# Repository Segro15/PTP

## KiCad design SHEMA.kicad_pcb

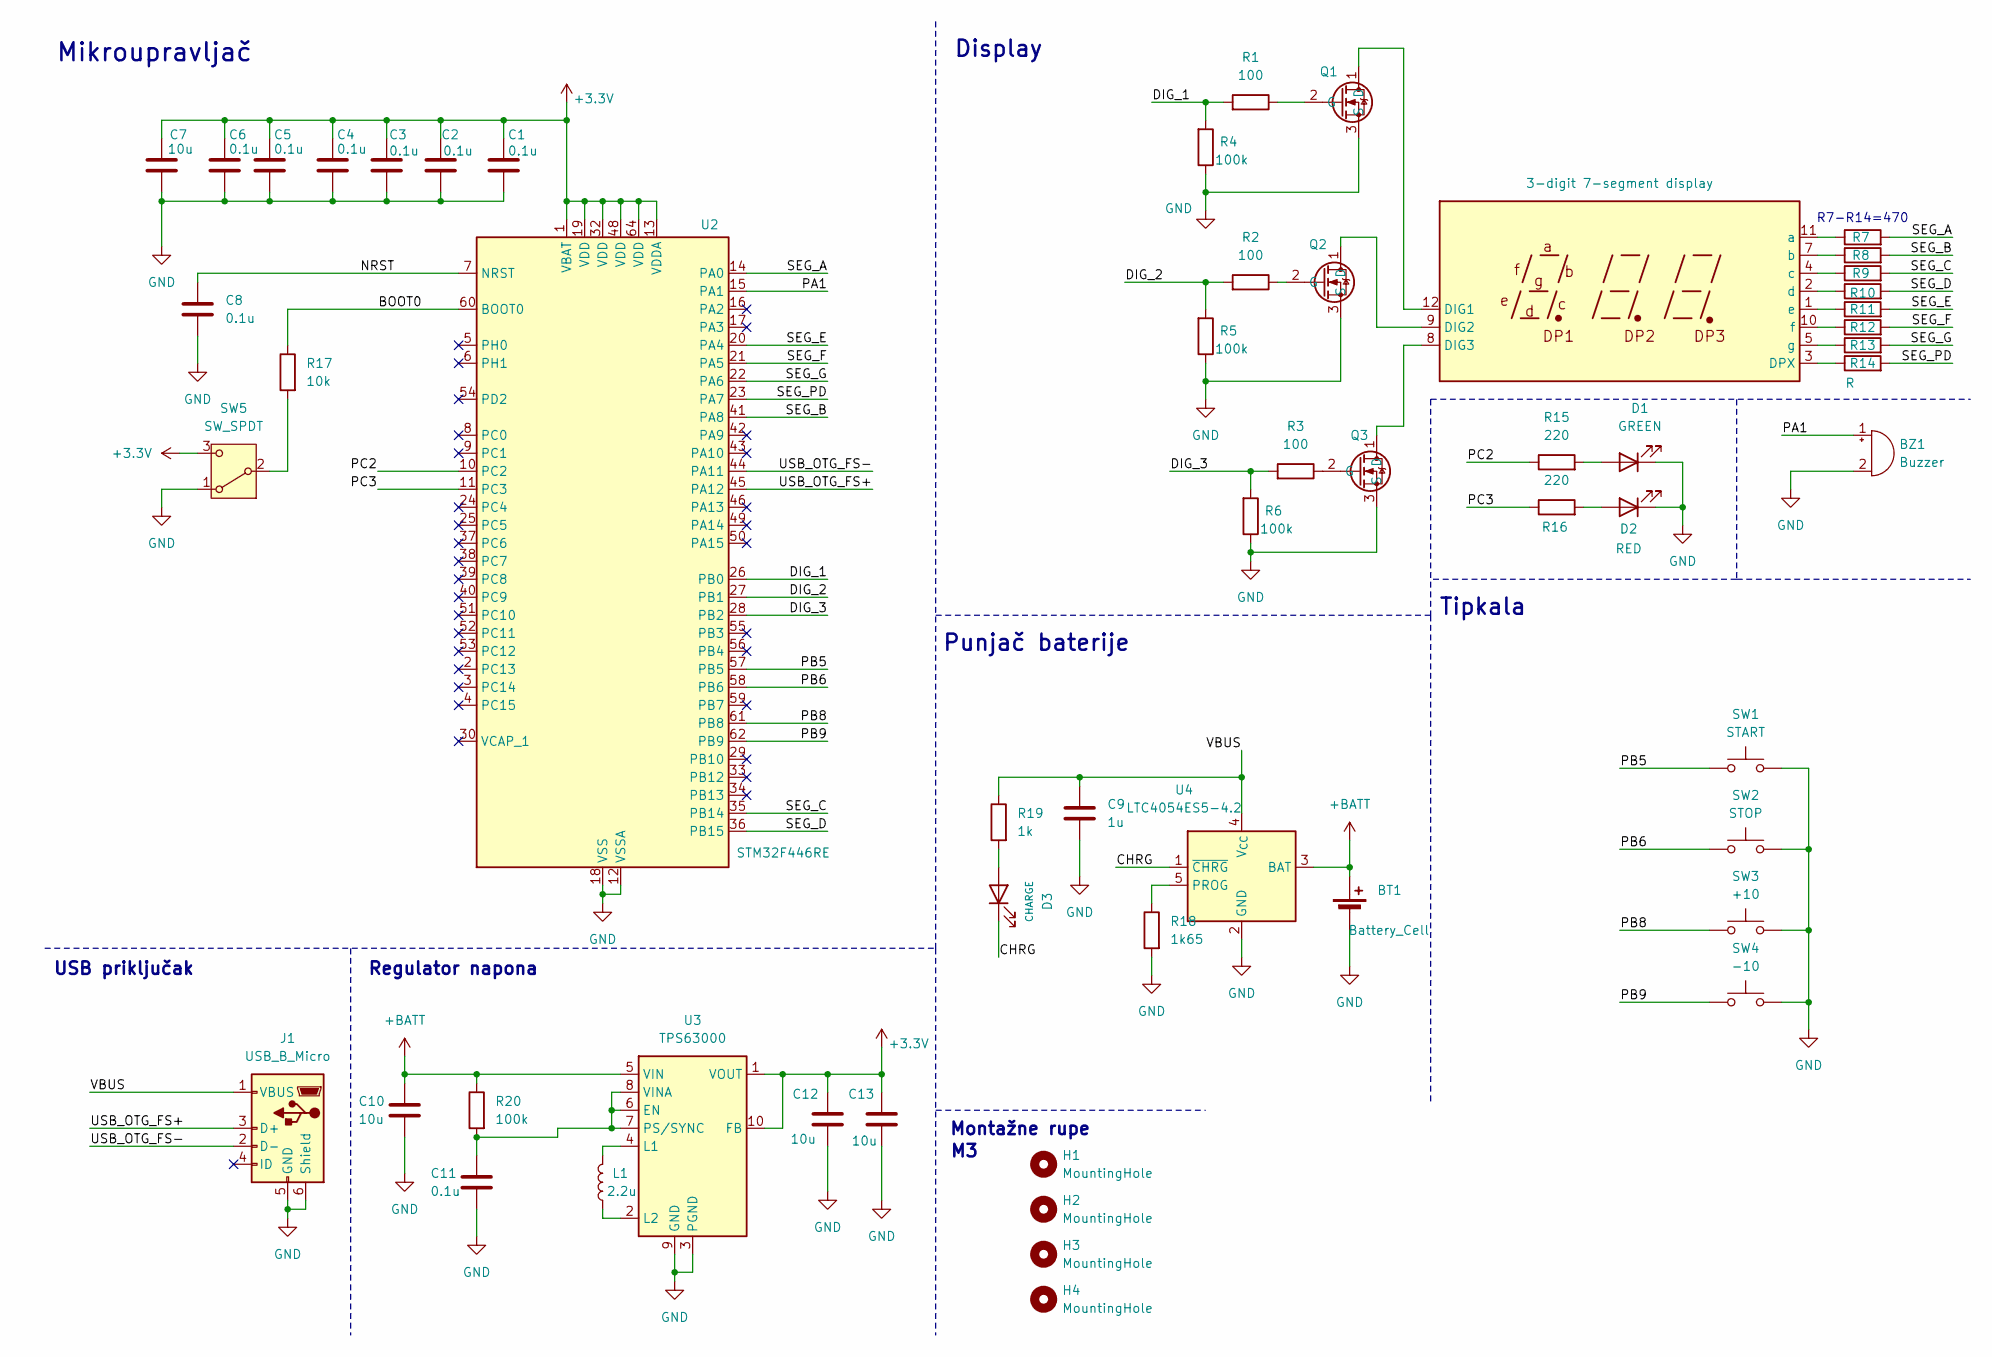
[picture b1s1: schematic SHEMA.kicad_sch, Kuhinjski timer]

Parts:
BT1: Battery_Cell; BatteryHolder_Keystone_1042_1x18650
BZ1: Buzzer; MagneticBuzzer_PUI_AT-0927-TT-6-R
C1, C2, C3, C4, C5, C6, C8, C11: 0.1u; C_0402_1005Metric
C7, C10, C12, C13: 10u; C_0603_1608Metric
C9: 1u; C_0402_1005Metric
D1: GREEN; LED_D5.0mm_FlatTop
D2: RED; LED_D5.0mm_FlatTop
D3: CHARGE; LED_D5.0mm_FlatTop
H1, H2, H3, H4: MountingHole; MountingHole_3.2mm_M3_DIN965
J1: USB_B_Micro; USB_Micro-B_Wuerth_629105150521
L1: 2.2u; L_TDK_MLZ2012_h0.85mm
Q1, Q2, Q3: BS170; TO-92
R1, R2, R3: 100; R_1206_3216Metric
R4, R5, R6: 100k; R_1206_3216Metric
R7, R8, R9, R10, R11, R12, R13, R14: R; R_1206_3216Metric
R15, R16: 220; R_0805_2012Metric
R17: 10k; R_0805_2012Metric
R18: 1k65; R_0805_2012Metric
R19: 1k; R_0805_2012Metric
R20: 100k; R_0805_2012Metric
SW1: START; SW_PUSH_1P1T_6x3.5mm_H4.3_APEM_MJTP1243
SW2: STOP; SW_PUSH_1P1T_6x3.5mm_H4.3_APEM_MJTP1243
SW3: +10; SW_PUSH_1P1T_6x3.5mm_H4.3_APEM_MJTP1243
SW4: -10; SW_PUSH_1P1T_6x3.5mm_H4.3_APEM_MJTP1243
SW5: SW_SPDT; SW_SPDT_PCM12
U1: 3-digit 7-segment display; LED_BA56-12SRWA
U2: STM32F446RE; LQFP-64_10x10mm_P0.5mm
U3: TPS63000; Texas_DRC0010J_ThermalVias
U4: LTC4054ES5-4.2; TSOT-23-5

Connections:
+3.3V: C1.1, C2.1, C3.1, C4.1, C5.1, C6.1, C7.1, C12.1, C13.1, SW5.3 (C), U2.1 (VBAT), U2.13 (VDDA), U2.19 (VDD), U2.32 (VDD), U2.48 (VDD), U2.64 (VDD), U3.1 (VOUT), U3.10 (FB); also elsewhere on the board
+BATT: BT1.1 (+), C10.1, R20.1, U3.5 (VIN), U4.3 (BAT); also elsewhere on the board
/BOOT0: R17.1, U2.60 (BOOT0)
/CHRG: D3.1 (K), U4.1 (~CHRG)
/DIG_1: R1.2, R4.2, U2.26 (PB0)
/DIG_2: R2.2, R5.2, U2.27 (PB1)
/DIG_3: R3.2, R6.2, U2.28 (PB2)
/NRST: C8.1, U2.7 (NRST)
/PA1: BZ1.1 (+), U2.15 (PA1)
/PB5: SW1.1, U2.57 (PB5)
/PB6: SW2.1, U2.58 (PB6)
/PB8: SW3.1, U2.61 (PB8)
/PB9: SW4.1, U2.62 (PB9)
/PC2: R15.1, U2.10 (PC2)
/PC3: R16.1, U2.11 (PC3)
/SEG_A: R7.2, U2.14 (PA0)
/SEG_B: R8.2, U2.41 (PA8)
/SEG_C: R9.2, U2.35 (PB14)
/SEG_D: R10.2, U2.36 (PB15)
/SEG_E: R11.2, U2.20 (PA4)
/SEG_F: R12.2, U2.21 (PA5)
/SEG_G: R13.2, U2.22 (PA6)
/SEG_PD: R14.2, U2.23 (PA7)
/USB_OTG_FS+: J1.3 (D+), U2.45 (PA12)
/USB_OTG_FS-: J1.2 (D-), U2.44 (PA11)
/VBUS: C9.1, J1.1 (VBUS), R19.1, U4.4 (V_{CC})
GND: BT1.2 (-), BZ1.2 (-), C1.2, C2.2, C3.2, C4.2, C5.2, C6.2, C7.2, C8.2, C9.2, C10.2, C11.2, C12.2, C13.2, D1.1 (K), D2.1 (K), J1.5 (GND), J1.6 (Shield), Q1.3 (S), Q2.3 (S), Q3.3 (S), R4.1, R5.1, R6.1, R18.2, SW1.2, SW2.2, SW3.2, SW4.2, SW5.1 (A), U2.12 (VSSA), U2.18 (VSS), U2.31 (VSS), U2.47 (VSS), U2.63 (VSS), U3.3 (PGND), U3.9 (GND), U3.11 (PGND), U4.2 (GND); also elsewhere on the board
unnamed: D1.2 (A), R15.2
unnamed: D2.2 (A), R16.2
unnamed: D3.2 (A), R19.2
unnamed: Q1.1 (D), U1.12 (DIG1)
unnamed: Q1.2 (G), R1.1
unnamed: Q2.1 (D), U1.9 (DIG2)
unnamed: Q2.2 (G), R2.1
unnamed: Q3.1 (D), U1.8 (DIG3)
unnamed: Q3.2 (G), R3.1
unnamed 36: R17.2, SW5.2 (B); also elsewhere on the board
unnamed: R14.1, U1.3 (DPX)
unnamed: R7.1, U1.11 (a)
unnamed: R8.1, U1.7 (b)
unnamed: R9.1, U1.4 (c)
unnamed: R10.1, U1.2 (d)
unnamed: R11.1, U1.1 (e)
unnamed: R12.1, U1.10 (f)
unnamed: R13.1, U1.5 (g)
unnamed: C11.1, R20.2, U3.6 (EN), U3.7 (PS/SYNC), U3.8 (VINA)
unnamed: L1.2, U3.4 (L1)
unnamed: L1.1, U3.2 (L2)
unnamed: R18.1, U4.5 (PROG)

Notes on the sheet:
R7-R14=470
Mikroupravljač
Tipkala
Display
Regulator napona
USB priključak
Punjač baterije
Montažne rupe

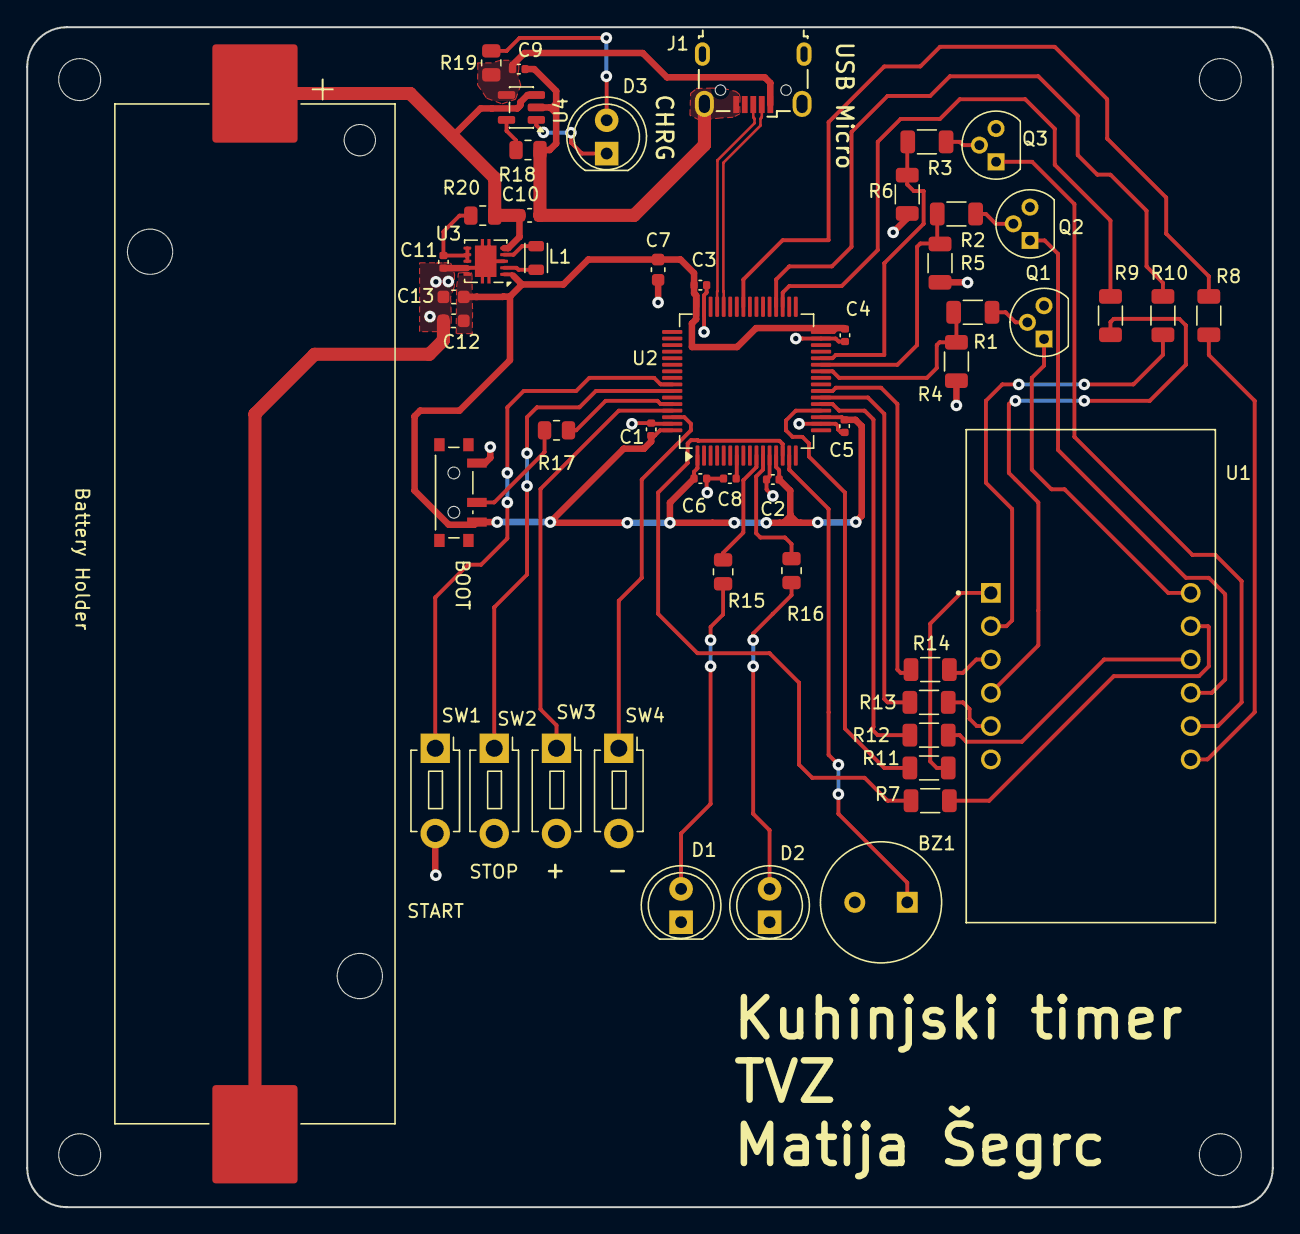
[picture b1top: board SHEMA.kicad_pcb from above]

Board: 2 copper layers, 95.0 x 90.0 mm, 56 parts (0 on the bottom side), 49 nets.

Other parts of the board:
BOOT: SW_SPDT; SW_SPDT_PCM12
Battery Holder: Battery_Cell; BatteryHolder_Keystone_1042_1x18650

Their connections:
+3.3V: BOOT.3 (C); also elsewhere on the board
+BATT: Battery Holder.1 (+); also elsewhere on the board
GND: BOOT.1 (A), Battery Holder.2 (-); also elsewhere on the board
unnamed 36: BOOT.2 (B); also elsewhere on the board

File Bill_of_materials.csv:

Reference;Quantity;Manufacturers Part Number;Manufacturer;Value;Footprint
BT1;1;1042;Keystone;~;Battery:BatteryHolder_Keystone_1042_1x18650
BZ1;1;AT?0927?TT?6?R;PUIaudio;~;Buzzer_Beeper:MagneticBuzzer_PUI_AT-0927-TT-6-R
C1,C2,C3,C4,C5,C6,C8,C11;8;~;~;0.1u;Capacitor_SMD:C_0402_1005Metric
C7,C10,C12,C13;4;~;~;10u;Capacitor_SMD:C_0603_1608Metric
C9;1;~;~;1u;Capacitor_SMD:C_0402_1005Metric
D1,D2,D3;3;~;~;~;LED_THT:LED_D5.0mm_FlatTop
J1;1;6,29105E+11;Wuerth;USB_B_Micro;Connector_USB:USB_Micro-B_Wuerth_629105150521
L1;1;MLZ2012;TDK;2.2u;Inductor_SMD:L_TDK_MLZ2012_h0.85mm
Q1,Q2,Q3;3;BS170-D26Z;Onsemi;BS170;Package_TO_SOT_THT:TO-92
R1,R2,R3;3;~;~;100;Resistor_SMD:R_1206_3216Metric
R4,R5,R6,R20;4;~;~;100k;Resistor_SMD:R_1206_3216Metric
R7,R8,R9,R10,R11,R12,R13,R14;8;~;~;470;Resistor_SMD:R_1206_3216Metric
R15,R16;2;~;~;220;Resistor_SMD:R_0805_2012Metric
R17;1;~;~;10k;Resistor_SMD:R_0805_2012Metric
R18;1;~;~;1k65;Resistor_SMD:R_0805_2012Metric
R19;1;~;~;1k;Resistor_SMD:R_0805_2012Metric
SW1,SW2,SW3,SW4;4;MJTP1243;Apem;Button Switch;Button_Switch_THT:SW_PUSH_1P1T_6x3.5mm_H4.3_APEM_MJTP1243
SW5;1;PCM12;Littelfuse;SPDT;Button_Switch_SMD:SW_SPDT_PCM12
U1;1;MP006832;Onsemi;3-digit 7-segment display;Display_7Segment:CA56-12CGKWA
U2;1;STM32F446RE;STM32;~;Package_QFP:LQFP-64_10x10mm_P0.5mm
U3;1;TPS63000;Texas Instruments;~;Package_SON:Texas_DRC0010J_ThermalVias
U4;1;LTC4054ES5-4.2;Linear Tehnology;~;Package_TO_SOT_SMD:TSOT-23-5
